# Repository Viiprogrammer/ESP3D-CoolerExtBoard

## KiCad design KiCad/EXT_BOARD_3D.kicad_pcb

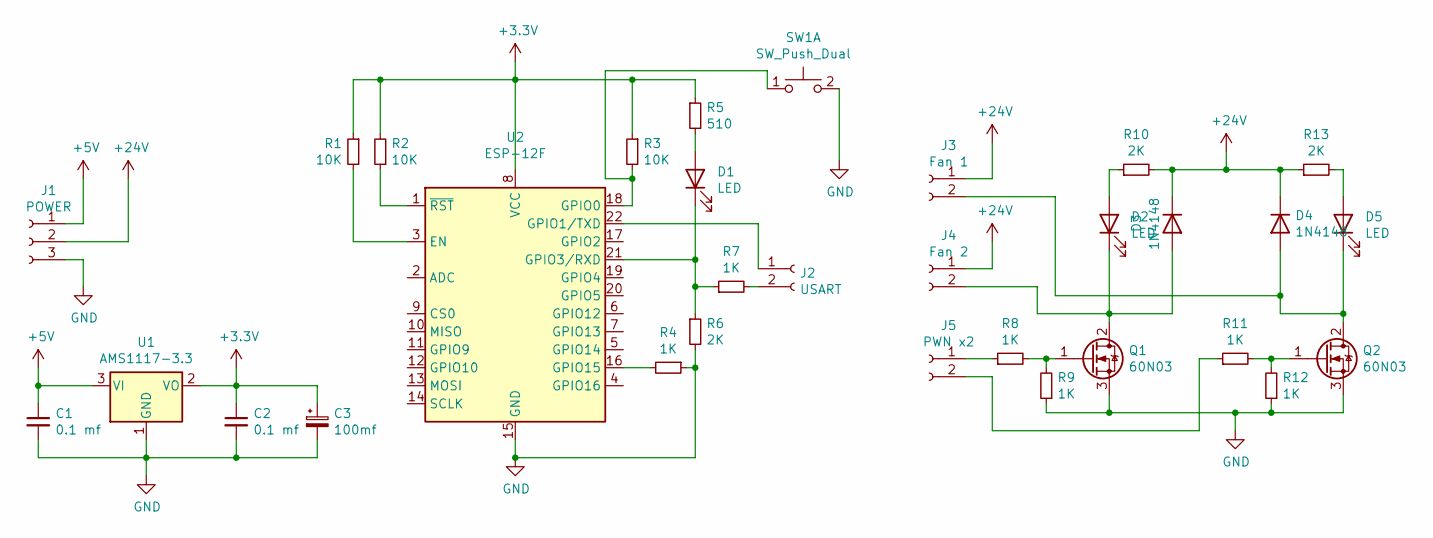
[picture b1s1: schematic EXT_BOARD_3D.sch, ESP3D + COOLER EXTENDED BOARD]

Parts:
C1, C2: 0.1 mf; C_1206_3216Metric
C3: 100mf; CP_Radial_D8.0mm_P3.80mm
D1, D2, D5: LED; LED_0805_2012Metric_Pad1.15x1.40mm_HandSolder
D3, D4: 1N4148; D_1206_3216Metric_Castellated
J1: POWER; PinHeader_1x03_P2.54mm_Vertical
J2: USART; PinHeader_2x01_P2.54mm_Vertical
J3: Fan 1; PinHeader_2x01_P2.54mm_Vertical
J4: Fan 2; PinHeader_2x01_P2.54mm_Vertical
J5: PWN x2; PinHeader_2x01_P2.54mm_Vertical
Q1, Q2: 60N03; TO-263-2
R1, R2, R3: 10K; R_1206_3216Metric_Pad1.42x1.75mm_HandSolder
R4, R7, R8, R9, R11, R12: 1K; R_1206_3216Metric_Pad1.42x1.75mm_HandSolder
R5: 510; R_1206_3216Metric_Pad1.42x1.75mm_HandSolder
R6, R10, R13: 2K; R_1206_3216Metric_Pad1.42x1.75mm_HandSolder
SW1: SW_Push_Dual; SW_PUSH_6mm
U1: AMS1117-3.3; SOT-223-3_TabPin2
U2: ESP-12F; ESP-12E

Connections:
+3V3: C2.1, C3.1, R1.1, R2.2, R3.1, R5.1, U1.2 (VO), U2.8 (VCC)
+5V: C1.1, J1.1, U1.3 (VI)
+24V: D3.1 (K), D4.1 (K), J1.2, J3.1, J4.1, R10.2, R13.1
GND: C1.2, C2.2, C3.2, J1.3, Q1.3 (S), Q2.3 (S), R4.1, R6.2, R9.1, R12.1, SW1.2 (D), U1.1 (GND), U2.15 (GND)
unnamed: D1.1 (K), R6.1, R7.1, U2.21 (GPIO3/RXD)
unnamed: D1.2 (A), R5.2
unnamed: D2.1 (K), D3.2 (A), J4.2, Q1.2 (D)
unnamed: D2.2 (A), R10.1
unnamed: D4.2 (A), D5.1 (K), J3.2, Q2.2 (D)
unnamed: D5.2 (A), R13.2
unnamed: J2.1, U2.22 (GPIO1/TXD)
unnamed: J2.2, R7.2
unnamed: J5.1, R8.1
unnamed: J5.2, R11.1
unnamed: Q1.1 (G), R8.2, R9.2
unnamed: Q2.1 (G), R11.2, R12.2
unnamed: R1.2, U2.3 (EN)
unnamed: R2.1, U2.1 (~RST)
unnamed: R3.2, SW1.1 (C), U2.18 (GPIO0)
unnamed: R4.2, U2.16 (GPIO15)

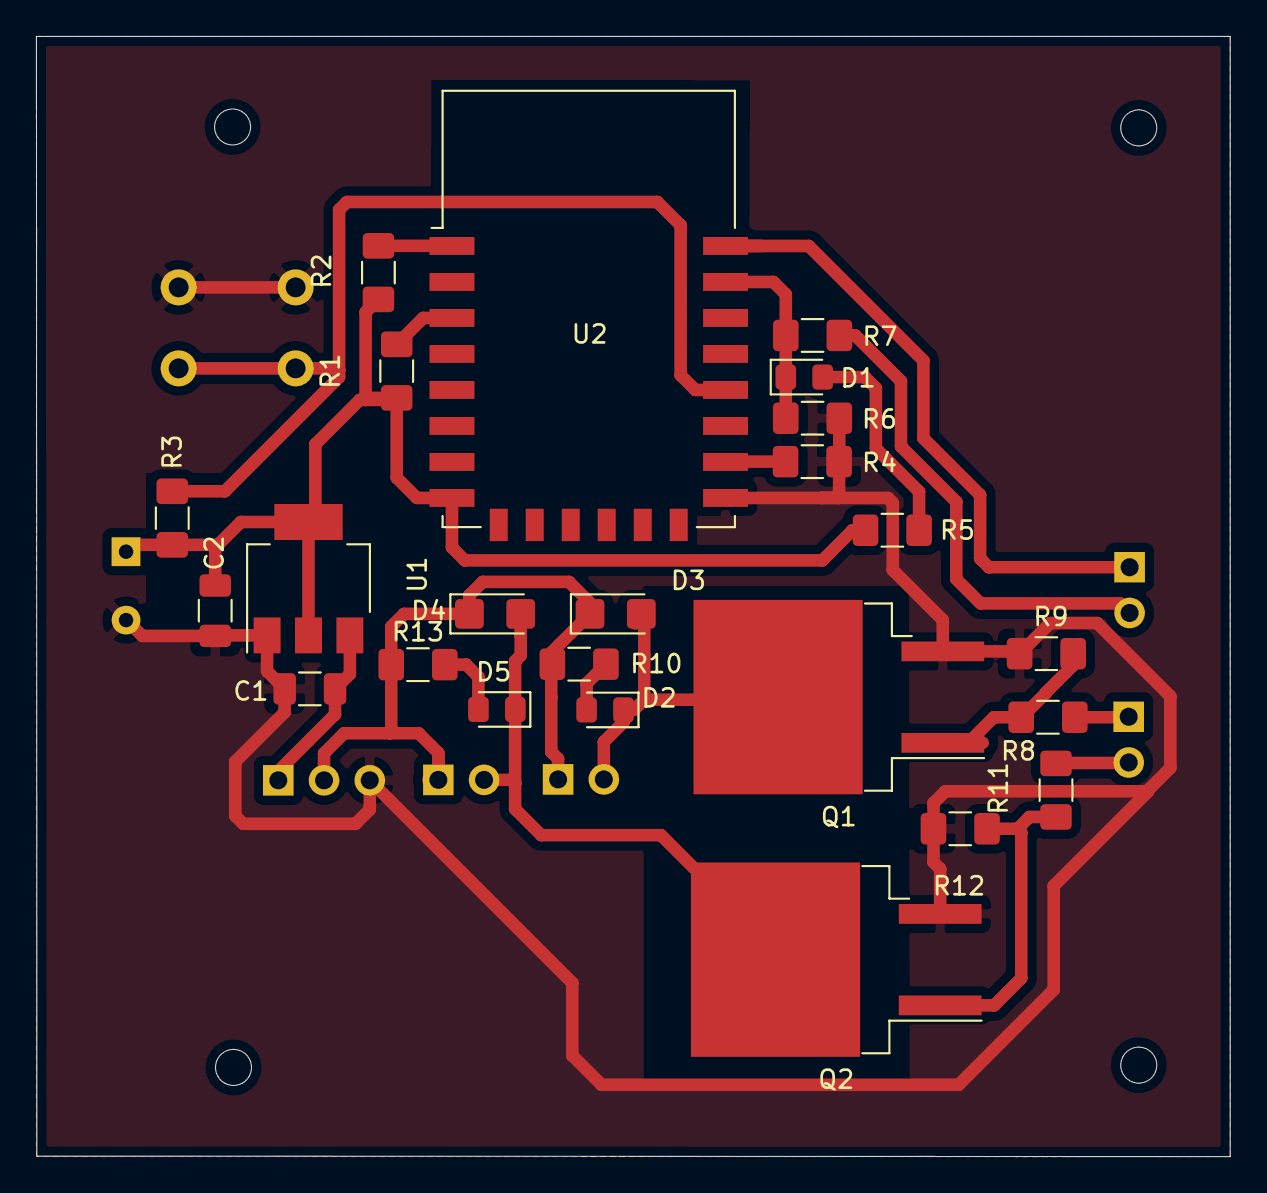
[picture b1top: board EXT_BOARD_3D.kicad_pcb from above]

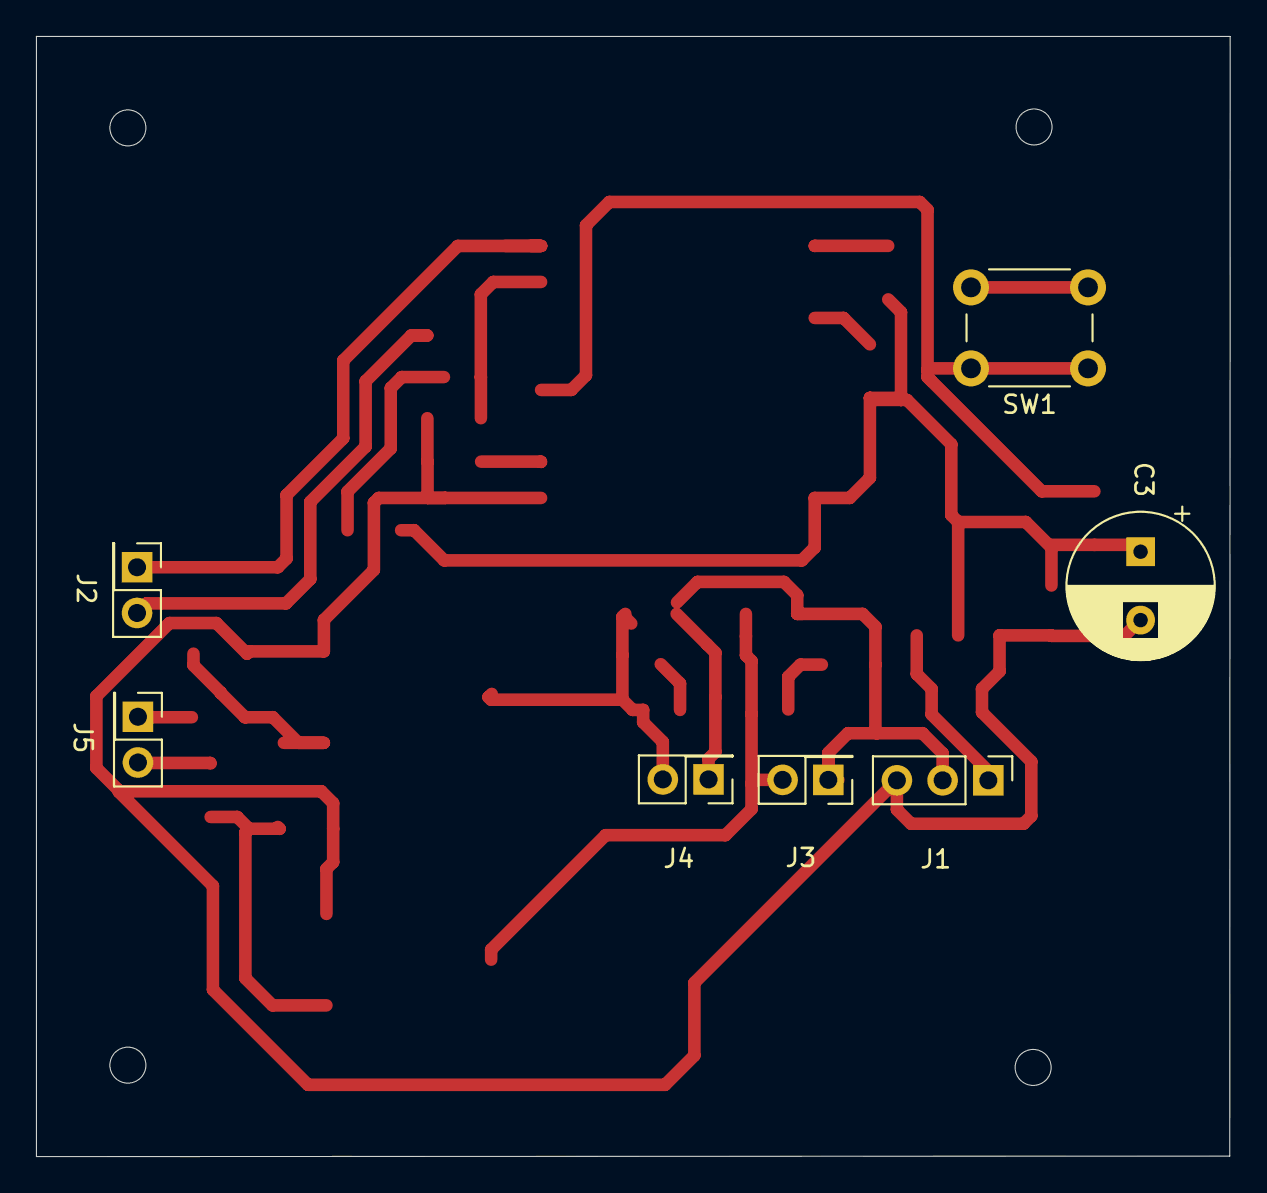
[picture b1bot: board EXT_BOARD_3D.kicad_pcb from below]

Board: 2 copper layers, 66.3 x 62.2 mm, 31 parts (7 on the bottom side), 20 nets.

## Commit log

2021-04-04 Added KiCad files
2021-04-04 Added HTML BOM
